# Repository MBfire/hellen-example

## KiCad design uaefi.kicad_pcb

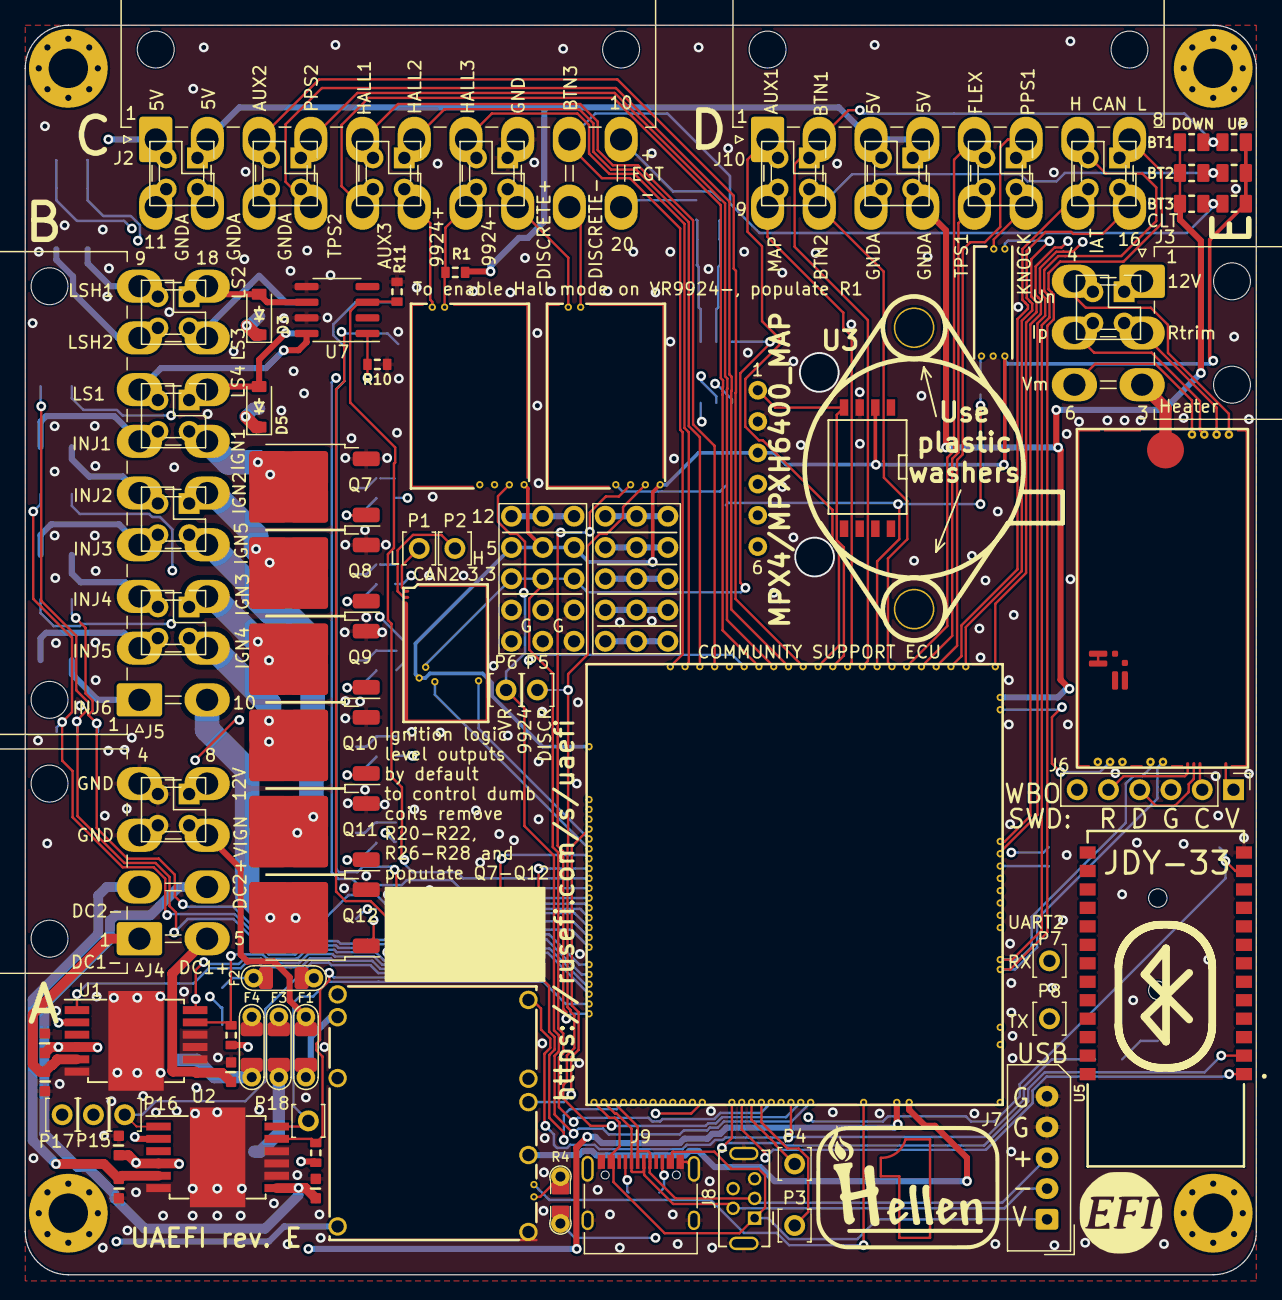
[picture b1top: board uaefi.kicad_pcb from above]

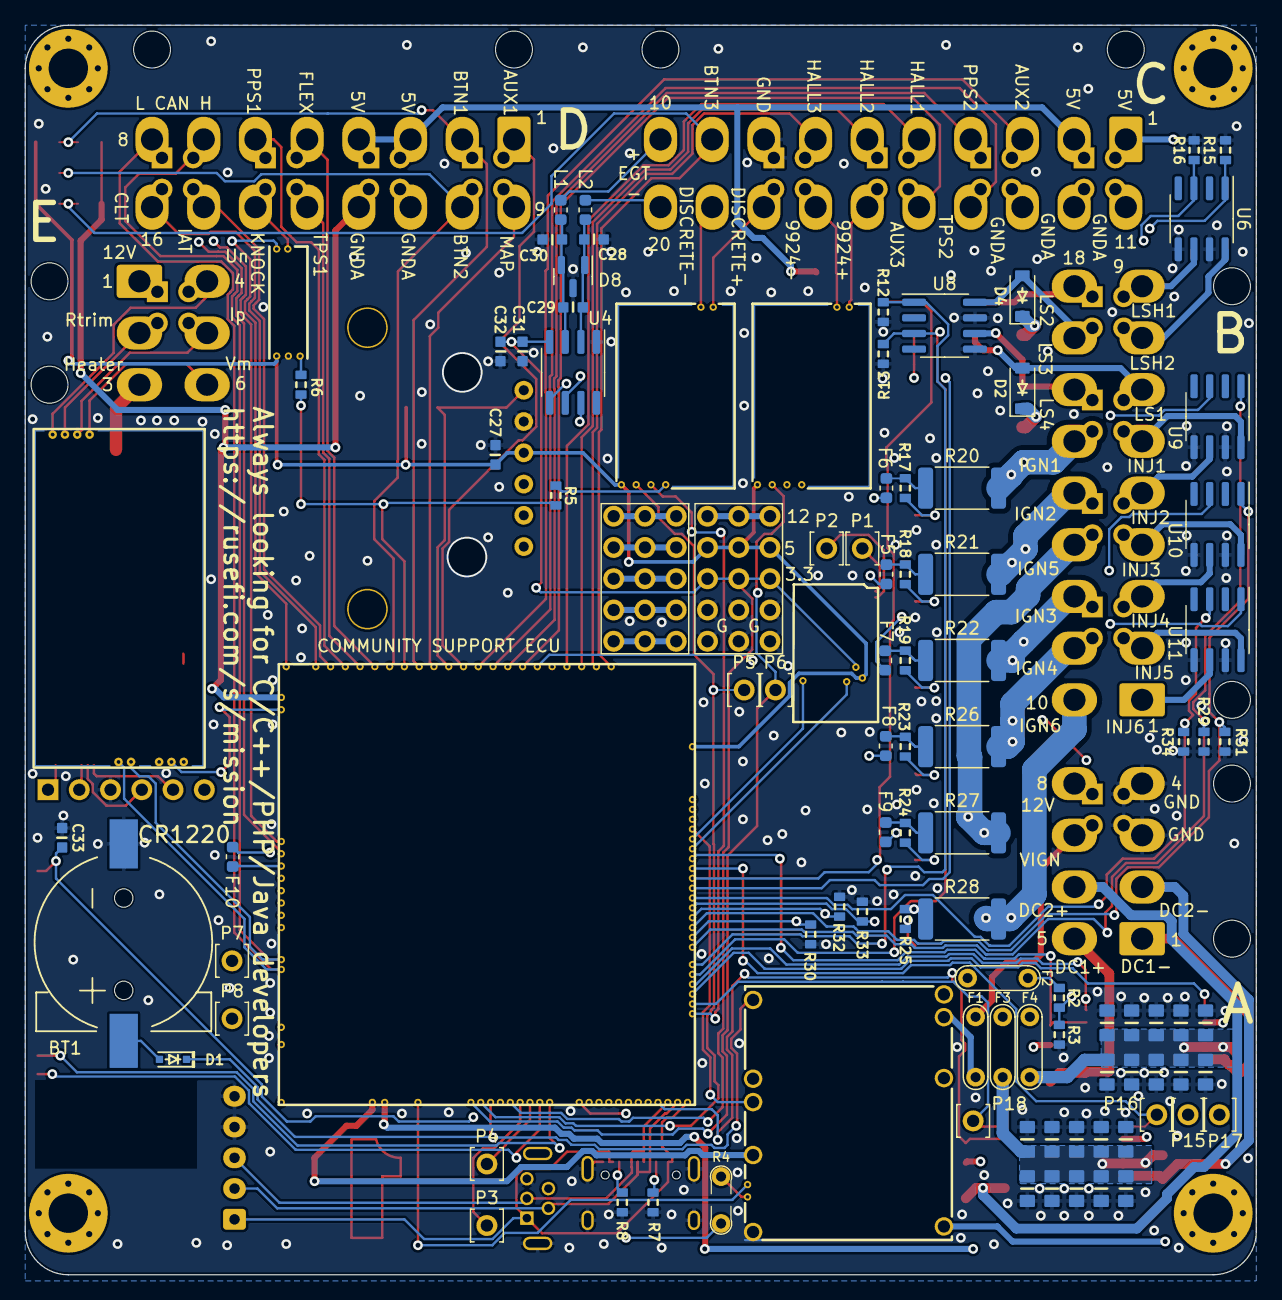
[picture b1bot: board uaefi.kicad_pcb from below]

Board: 4 copper layers, 100.0 x 101.5 mm, 159 parts (74 on the bottom side), 145 nets.

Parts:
BT1: CR1220; CR1220-2
C1, C2, C3, C4, C5, C6, C7, C8, C9, C10, C14, C15, C16, C17, C18, C19, C20, C21, C22, C23: 10u; C0805
C11, C24, C27, C29, C31, C33: 100n; C0603
C12, C13, C25, C26, C28, C30: 10n; C0603
C32: 1u; C0603
D1: 1N4148WS; SOD-323
D2, D3, D4, D5: B5819W; SOD-123
D8: NUP2105L; SOT-23
F1, F2, F3, F4: 12H1500D; PAD-1206-PAD
F5, F6, F7, F8, F9, F10: 50mA; Fuse_0603_1608Metric
G1: RUSEFI_LOGO; rusefi_logo
G2: LOGO
G3, G4: PROTO_AREA
H1, H2, H3, H4: M3; MountingHole_3.2mm_M3_Pad_Via
J1, J11, J12, J13, J14, J15, J16, J17, J18, J19, J20, J21, J22, J24: Conn_02x02_Odd_Even; PinSocket_2x02_P2.54mm_Vertical
J2: 5569-20A2; Molex_Mini-Fit_Jr_5569-20A2_2x10_P4.20mm_Horizontal
J3: 5569-06A2; Molex_Mini-Fit_Jr_5569-06A2_2x03_P4.20mm_Horizontal
J4: 5569-08A2; Molex_Mini-Fit_Jr_5569-08A2_2x04_P4.20mm_Horizontal
J5: 5569-18A2; Molex_Mini-Fit_Jr_5569-18A2_2x09_P4.20mm_Horizontal
J6: Conn_01x06; PinHeader_1x06_P2.54mm_Vertical
J7: Conn_01x05_Male; Molex_SPOX_5267-05A_1x05_P2.50mm_Vertical
J8: USB_B_Mini; USB-MINI-B-VERTICAL
J9: USB_C
J10: 5569-16A2; Molex_Mini-Fit_Jr_5569-16A2_2x08_P4.20mm_Horizontal
L1, L2: 470R@100MHz; L_0603_1608Metric
M1: Module-power_12and5V-0.3; power_12and5V
M2: Module-knock-0.2; knock
M3: Module-vr-discrete-0.5; vr-discrete
M4: Module-vr-max9924-0.1; vr-max9924
M5: Module-wbo-0.5; wbo
M6: Module:mega-mcu100/0.3; mega-mcu100
M7: Module-can-0.1; can
P1, P2, P3, P4, P5, P6, P7, P8, P15, P16, P17, P18: Pad; PAD-TH
Q7, Q8, Q9, Q10, Q11, Q12: ISL9V3040D3ST; TO-252-2
R1, R9, R10, R11, R12, R13, R14, R15, R16, R29, R30, R31, R32, R33, R34: 4.7k; R0603
R2: 33k; R0603
R3: 6.8k; R0603
R4: Jumper-Pad-Pad; PAD-0805-PAD
R5, R6: 0; R0603
R7, R8: 5.6k; R0603
R17, R18, R19, R23, R24, R25: 22; R0603
R20, R21, R22, R26, R27, R28: 0; R_2512_6332Metric
R35, R36, R37: 10k; R0805
R38, R39, R40: DNP; R0805
U1, U2: TLE9201SG; Infineon_PG-DSO-12-11
U3: MPX4/MPXH6400_MAP; MPX-4_MAP
U4: MAX31855KASA; SOIC-8_3.9x4.9mm_P1.27mm
U5: JDY-33
U6, U7, U8, U9, U10, U11: VNLD5160TR-E; SOIC-8_3.9x4.9mm_P1.27mm

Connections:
+3.3V: M6.N21 (V33), R9.2, R14.2, U1.2 (VSO), U2.2 (VSO)
+3.3VA: C31.2, C32.2, C33.2, G3.3, G3.8, G3.13, M6.N15 (V33_SWITCHABLE), M7.V2 (CAN_VIO), U4.4 (V_CC), U5.12 (3V3)
+5V: M1.E4 (V5), M6.N22 (VCC)
+5VA: C27.2, G3.4, G3.9, G3.14, M2.E1 (V5A), M3.E4 (V5_IN), M4.E4 (V5_IN), M5.W1 (V5_IN), M6.E1 (V5A_SWITCHABLE), M6.W2 (V5A_SWITCHABLE), M7.V1 (V5), R38.2, R39.2, R40.2, U3.3 (VCC)
+5VP: J2.1, J2.2, J10.3, J10.4, J12.1, J12.2, J14.1, J14.2, M1.V4 (5VP), R1.1
+12V: F2.1, F3.1, F4.1, J4.8, J22.1, R2.2
+12V_RAW: D2.1 (K), D3.1 (K), D4.1 (K), D5.1 (K), F2.2, G3.5, G3.10, G3.15, J3.1, J24.1, M1.V1 (V12_PERM), M1.V3 (V12_RAW)
/12V_KEY: F1.1, J4.7, J22.3
/ADC3: M6.S15 (IN_KNOCK_(PA2)), R5.2, R6.2
/CAN+: J1.2, J10.7, M5.W4 (CANH), M6.W11 (CANH)
/CAN-: J1.1, J10.8, M5.W3 (CANL), M6.W12 (CANL)
/DC1_DIR: M6.E21 (OUT_PWM4_(PC8)), P15.1, U1.1 (DIR)
/DC1_DIS: M6.E8 (SPI2_MISO_(PB14)), R9.1, U1.11 (DIS)
/DC1_PWM: M6.E20 (OUT_PWM3_(PC7)), P17.1, U1.12 (PWM)
/DC2_DIR: M6.E9 (SPI2_MOSI_(PB15)), P16.1, U2.1 (DIR)
/DC2_DIS: M6.N4 (USBID_(PA10)), R14.1, U2.11 (DIS)
/DC2_PWM: M6.E22 (OUT_PWM5_(PC9)), P18.1, U2.12 (PWM)
/DC Driver 1/PWR: C1.2, C2.2, C3.2, C4.2, C5.2, C6.2, C7.2, C8.2, C9.2, C10.2, C11.2, F4.2, U1.4 (VS)
/DC Driver 2/PWR: C14.2, C15.2, C16.2, C17.2, C18.2, C19.2, C20.2, C21.2, C22.2, C23.2, C24.2, F3.2, U2.4 (VS)
/EGT+: J2.10, L1.1
/EGT-: J2.20, L2.1
/EGT/SPI_CS: M6.N9 (SPI3_CS_(PA15)), U4.6 (~CS)
/IGN1: F6.2, M6.W10 (IGN1_(PC13))
/IGN2: F5.2, M6.W9 (IGN2_(PE5))
/IGN3: F7.2, M6.W8 (IGN3_(PE4))
/IGN4: F8.2, M6.W7 (IGN4_(PE3))
/IGN5: F9.2, M6.W6 (IGN5_(PE2))
/IGN6: F10.2, M6.W5 (IGN6_(PB8))
/INJ1: M6.E17 (OUT_INJ1_(PD3)), R29.2, U9.1 (IN1)
/INJ2: M6.E16 (OUT_INJ2_(PA9)), R30.2, U9.3 (IN2)
/INJ3: M6.E15 (OUT_INJ3_(PD11)), R31.2, U10.1 (IN1)
/INJ4: M6.E14 (OUT_INJ4_(PD10)), R32.2, U10.3 (IN2)
/INJ5: M6.E13 (OUT_INJ5_(PD2)), R33.2, U11.1 (IN1)
/INJ6: M6.E12 (OUT_INJ6_(PA8)), R34.2, U11.3 (IN2)
/INTERNAL_MAP: M6.S12 (IN_MAP2_(PC1)), U3.1 (VOUT)
/IN_AUX1: J10.1, J13.2, M6.S11 (IN_O2S_/_CAN_WAKEUP_(PA0))
/IN_AUX2: J2.3, J15.2, M6.S10 (IN_O2S2_(PA1))
/IN_AUX3: J2.15, J16.4, M6.S7 (IN_AUX3_(PA7))
/IN_BUTTON1: J10.2, J13.1, M6.S14 (IN_CRANK_(PB1)), R35.2, R38.1
/IN_BUTTON2: J10.10, J13.3, M6.S16 (IN_CAM_(PA6)), R36.2, R39.1
/IN_BUTTON3: J2.9, M6.S1 (IN_D4_(PE15)), R37.2, R40.1
/IN_CLT: J1.3, J10.16, M6.S21 (IN_CLT_(PC2))
/IN_FLEX: J10.5, J11.2, M6.S17 (IN_VSS_(PE11))
/IN_HALL1: J2.5, J16.2, M6.S4 (IN_D1_(PE12))
/IN_HALL2: J2.6, J16.1, M6.S3 (IN_D2_(PE13))
/IN_HALL3: J2.7, J17.2, M6.S2 (IN_D3_(PE14))
/IN_IAT: J1.4, J10.15, M6.S20 (IN_IAT_(PC3))
/IN_KNOCK: M2.E3 (OUT_KNOCK), R6.1
/IN_KNOCK_RAW: J10.14, J11.3, M2.W1 (IN_KNOCK)
/IN_MAP: J10.9, J13.4, M6.S13 (IN_MAP1_(PC0))
/IN_PPS1: J10.6, J11.1, M6.S19 (IN_PPS_(PA3))
/IN_PPS2: J2.4, J15.1, M6.S8 (IN_AUX2_(PC4/PE9))
/IN_TPS1: J10.13, J11.4, M6.S18 (IN_TPS_(PA4))
/IN_TPS2: J2.14, J15.3, M6.S9 (IN_AUX1_(PB0))
/IN_VIGN: F1.2, M1.V2 (IN_VIGN)
/IN_VMAIN: M6.S6 (IN_AUX4_(PC5)), R2.1, R3.2
/LS1: M6.E11 (OUT_INJ7_(PD15)), R10.2, U7.1 (IN1)
/LS2: M6.E10 (OUT_INJ8_(PD12)), R11.2, U7.3 (IN2)
/LS3: M6.E18 (OUT_PWM1_(PD13)), R12.2, U8.1 (IN1)
/LS4: M6.E19 (OUT_PWM2_(PC6)), R13.2, U8.3 (IN2)
/LS_HOT1: M6.W4 (IGN7_(PB9)), R16.1, U6.3 (IN2)
/LS_HOT2: M6.W3 (IGN8_(PE6)), R15.1, U6.1 (IN1)
/MISO3: M6.N11 (SPI3_MISO_(PC11)), U4.7 (SO)
/OUT_DC1+: C13.2, J4.5, U1.7 (OUT2)
/OUT_DC1-: C12.2, J4.1, U1.5 (OUT1)
/OUT_DC2+: C26.2, J4.6, U2.7 (OUT2)
/OUT_DC2-: C25.2, J4.2, U2.5 (OUT1)
/OUT_IGN1: J5.15, J19.3, Q7.2 (C), R20.2
/OUT_IGN2: J5.14, J20.1, Q8.2 (C), R21.2
/OUT_IGN3: J5.12, J21.1, Q9.2 (C), R22.2
/OUT_IGN4: J5.11, J21.3, Q10.2 (C), R26.2
/OUT_IGN5: J5.13, J20.3, Q11.2 (C), R27.2
/OUT_IGN6: J5.10, Q12.2 (C), R28.2
/OUT_INJ1: J5.6, J19.4, U9.8 (D1)
/OUT_INJ2: J5.5, J20.2, U9.6 (D2)
/OUT_INJ3: J5.4, J20.4, U10.8 (D1)
/OUT_INJ4: J5.3, J21.2, U10.6 (D2)
/OUT_INJ5: J5.2, J21.4, U11.8 (D1)
/OUT_INJ6: J5.1, U11.6 (D2)
/OUT_LS1: D2.2 (A), J5.7, J19.2, U7.8 (D1)
/OUT_LS2: D3.2 (A), J5.18, J18.1, U7.6 (D2)
/OUT_LS3: D4.2 (A), J5.17, J18.3, U8.8 (D1)
/OUT_LS4: D5.2 (A), J5.16, J19.1, U8.6 (D2)
/OUT_LS_HOT1: J5.9, J18.2, U6.6 (D2)
/OUT_LS_HOT2: J5.8, J18.4, U6.8 (D1)
/PG_5VP: M6.N12 (SPI3_MOSI_(PC12)), R4.2
/PWR_EN: M1.E5 (EN_5VP), M6.N20 (OUT_PWR_EN_(PE10))
/SCK3: M6.N10 (SPI3_SCK_(PC10)), U4.5 (SCK)
/USB+: J7.3, J8.3 (D+), J9.A6 (D+), J9.B6 (D+), M6.N3 (USBP_(PA12))
/USB-: J7.2, J8.2 (D-), J9.A7 (D-), J9.B7 (D-), M6.N2 (USBM_(PA11))
/VBAT: D1.1 (K), M1.E1 (VBAT), M6.N17 (VBAT)
/VBUS: J7.1, J8.1 (VBUS), J9.A4 (VBUS), J9.A9 (VBUS), J9.B4 (VBUS), J9.B9 (VBUS), M6.N1 (VBUS)
/VIGN: M1.E3 (VIGN), M6.E5 (IN_VIGN_(PA5))
/VREF1: M2.W2 (VREF), M6.S22 (VREF1)
/VR_DISCRETE: M3.E3 (OUT), M6.N18 (UART8_RX_(PE0)), P5.1
/VR_DISCRETE+: J2.18, J17.3, M3.W2 (VR+)
/VR_DISCRETE-: J2.19, M3.W1 (VR-)
/VR_DISCRETE_A: M3.E2 (OUT_A), R5.1
/VR_DISCRETE_THR: M3.E1 (Thresh_IN), M6.E23 (OUT_PWM6_(PD14))
/VR_MAX9924: M4.E3 (OUT), M6.N19 (UART8_TX_(PE1)), P6.1
/VR_MAX9924+: J2.16, J16.3, M4.W2 (VR+)
/VR_MAX9924-: J2.17, J17.4, M4.W1 (VR-), R1.2
/WBO_Heater: J3.3, M5.E5 (LSU_H+)
/WBO_Ip: J3.5, J24.4, M5.E3 (LSU_Ip)
/WBO_Rtrim: J3.2, J24.3, M5.E4 (LSU_Rtrim)
/WBO_Un: J3.4, J24.2, M5.E1 (LSU_Un)
/WBO_Vm: J3.6, M5.E2 (LSU_Vm)
GND: BT1.2 (-), C1.1, C2.1, C3.1, C4.1, C5.1, C6.1, C7.1, C8.1, C9.1, C10.1, C11.1, C12.1, C13.1, C14.1, C15.1, C16.1, C17.1, C18.1, C19.1, C20.1, C21.1, C22.1, C23.1, C24.1, C25.1, C26.1, C27.1, C28.1, C30.1, C31.1, C32.1, C33.1, D8.3 (A), G3.1, G3.2, G3.6, G3.7, G3.11, G3.12, J2.8, J4.3, J4.4, J6.3, J7.4, J7.5, J8.5 (GND), J8.6 (Shield), J9.A1 (GND), J9.A12 (GND), J9.B1 (GND), J9.B12 (GND), J9.S1 (SHIELD), J17.1, J22.2, J22.4, M1.S1 (GND), M2.E2 (GND), M3.G (GND), M4.G (GND), M5.E6 (LSU_H-), M5.G (GND), M6.G (GND), M7.E1 (GND), Q7.3 (E), Q8.3 (E), Q9.3 (E), Q10.3 (E), Q11.3 (E), Q12.3 (E), R3.1, R7.1, R8.1, R10.1, R11.1, R12.1, R13.1, R15.2, R16.2, R29.1, R30.1, R31.1, R32.1, R33.1, R34.1, U1.6 (GND), U1.8 (SI), U1.9 (CSN), U1.10 (SCK), U1.13 (GND), U2.6 (GND), U2.8 (SI), U2.9 (CSN), U2.10 (SCK), U2.13 (GND), U3.2 (GND), U4.1 (GND), U5.13 (GND), U6.5 (S2), U6.7 (S1), U7.5 (S2), U7.7 (S1), U8.5 (S2), U8.7 (S1), U9.5 (S2), U9.7 (S1), U10.5 (S2), U10.7 (S1), U11.5 (S2), U11.7 (S1)
GNDA: J2.11, J2.12, J2.13, J10.11, J10.12, J12.3, J12.4, J14.3, J14.4, J15.4, M6.W1 (GNDA), R35.1, R36.1, R37.1
unnamed: BT1.1 (+), D1.2 (A)
unnamed: F5.1, R18.2, R21.1
unnamed: F6.1, R17.2, R20.1
unnamed: F7.1, R19.2, R22.1
unnamed: F8.1, R23.2, R26.1
unnamed: F9.1, R24.2, R27.1
unnamed: F10.1, R25.2, R28.1
unnamed: G4.1, G4.6, G4.11
unnamed: G4.5, G4.10, G4.15
unnamed: G4.2, G4.7, G4.12
unnamed: G4.3, G4.8, G4.13
unnamed: G4.4, G4.9, G4.14
unnamed: J6.1, M5.W8 (V33_OUT)
unnamed: J6.2, M5.W7 (SWCLK)
unnamed: J6.4, M5.W6 (SWDIO)
unnamed: J6.5, M5.W5 (nReset)
unnamed: J9.A5 (CC1), R7.2
unnamed: J9.B5 (CC2), R8.2
unnamed: M1.E6 (PG_5VP), R4.1
unnamed: M5.J1 (SEL1), M5.J_GND1 (PULL_DOWN1)
unnamed: M6.N14a (LED_GREEN), P4.1
unnamed: M6.N14b (LED_YELLOW), P3.1
unnamed: M6.E6 (SPI2_CS_/_CAN2_RX_(PB12)), M7.V6 (CAN_RX)
unnamed: M6.E7 (SPI2_SCK_/_CAN2_TX_(PB13)), M7.V5 (CAN_TX)
unnamed: M6.N14 (UART2_RX_(PD6)), P7.1, U5.1 (TXD)
unnamed: M6.N13 (UART2_TX_(PD5)), P8.1, U5.2 (RXD)
unnamed: M7.S2 (CANH), P2.1
unnamed: M7.S1 (CANL), P1.1
unnamed: Q7.1 (G), R17.1
unnamed: Q8.1 (G), R18.1
unnamed: Q9.1 (G), R19.1
unnamed: Q10.1 (G), R23.1
unnamed: Q11.1 (G), R24.1
unnamed: Q12.1 (G), R25.1
unnamed: C29.2, C30.2, D8.2 (K), L1.2, U4.3 (T+)
unnamed: C28.2, C29.1, D8.1 (K), L2.2, U4.2 (T-)

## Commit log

2026-02-13 Update BOARD_PREFIX and BOARD_SUFFIX values
2026-02-13 GHA says update kicad6-libraries
2026-02-13 GHA says update hellen-one
2026-02-13 Change BOARD_SUFFIX from 'e' to '-'
2026-02-13 Update BOARD_SUFFIX and BOARD_REVISION values
2026-02-13 Update BOARD_SUFFIX to include '-e'
2026-02-13 Update BOARD_PREFIX, BOARD_SUFFIX, and BOARD_REVISION
2026-02-26 uaefi kicad test added
2026-02-26 replace
2026-02-26 [skip actions] Auto-generated board v2.1
2026-04-23 Remove BOARD_PREFIX and modify BOARD_SUFFIX
    Removed BOARD_PREFIX and updated BOARD_SUFFIX.
